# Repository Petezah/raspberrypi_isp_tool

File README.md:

# raspberrypi_isp_tool
PCB design for an AVR In-System Programmer tool for the Raspberry Pi

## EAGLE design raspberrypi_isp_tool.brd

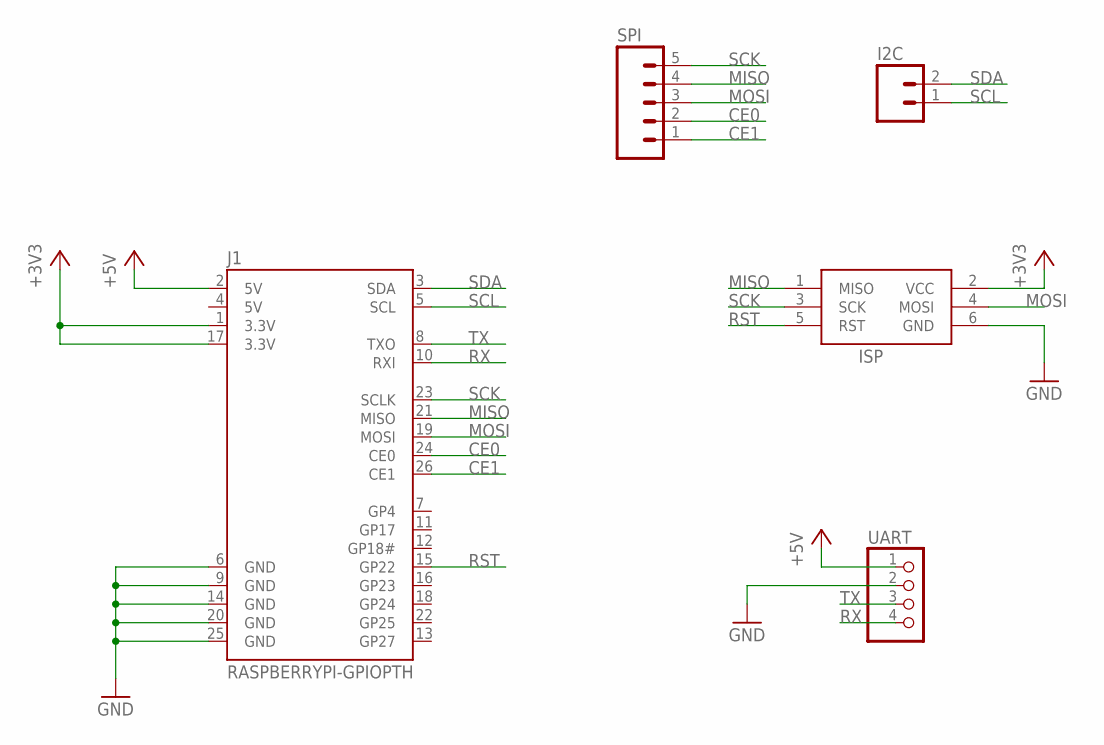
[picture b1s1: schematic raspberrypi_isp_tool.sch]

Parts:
I2C: M02PTH; 1X02
ISP: AVRISP-6; AVRISP
J1: RASPBERRYPI-GPIOPTH; 2X13-SHROUDED
SPI: M05PTH; 1X05
UART: PINHD-1X4; 1X04

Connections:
5V: J1.4 (5V)
+3V3: ISP.2 (VCC), J1.1 (3.3V), J1.17 (3.3V)
+5V: J1.2 (5V), UART.1
CE0: J1.24 (CE0), SPI.2
CE1: J1.26 (CE1), SPI.1
GND: ISP.6 (GND), J1.6 (GND), J1.9 (GND), J1.14 (GND), J1.20 (GND), J1.25 (GND), UART.2
MISO: ISP.1 (MISO), J1.21 (MISO), SPI.4
MOSI: ISP.4 (MOSI), J1.19 (MOSI), SPI.3
RST: ISP.5 (RST), J1.15 (GP22)
RX: J1.10 (RXI), UART.4
SCK: ISP.3 (SCK), J1.23 (SCLK), SPI.5
SCL: I2C.1, J1.5 (SCL)
SDA: I2C.2, J1.3 (SDA)
TX: J1.8 (TXO), UART.3

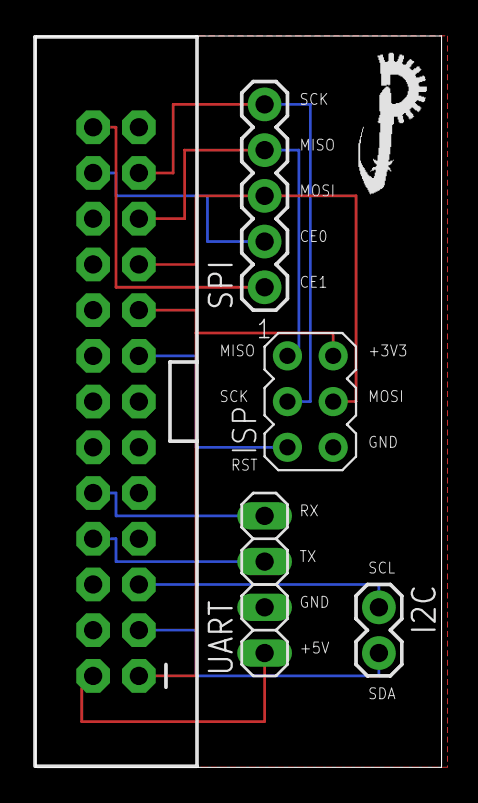
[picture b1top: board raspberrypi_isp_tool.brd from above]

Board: 2 copper layers, 22.5 x 40.6 mm, 7 parts (1 on the bottom side), 13 nets.

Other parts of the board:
U$1: LOGO_TINY
U$2: LOGO_SM

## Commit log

2016-06-07 Initial commit of project Contains only the GPIO header for the raspberry pi so far
2016-06-15 More work on breakout utility
2016-06-24 Finished layout for rev a

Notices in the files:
raspberrypi_isp_tool.brd:
(c) 2016 Peter Dunshee
parts and their libraries:
SparkFun-Connectors: Licensing: Creative Commons ShareAlike 4.0 International - https://creativecommons.org/licenses/by-sa/4.0
